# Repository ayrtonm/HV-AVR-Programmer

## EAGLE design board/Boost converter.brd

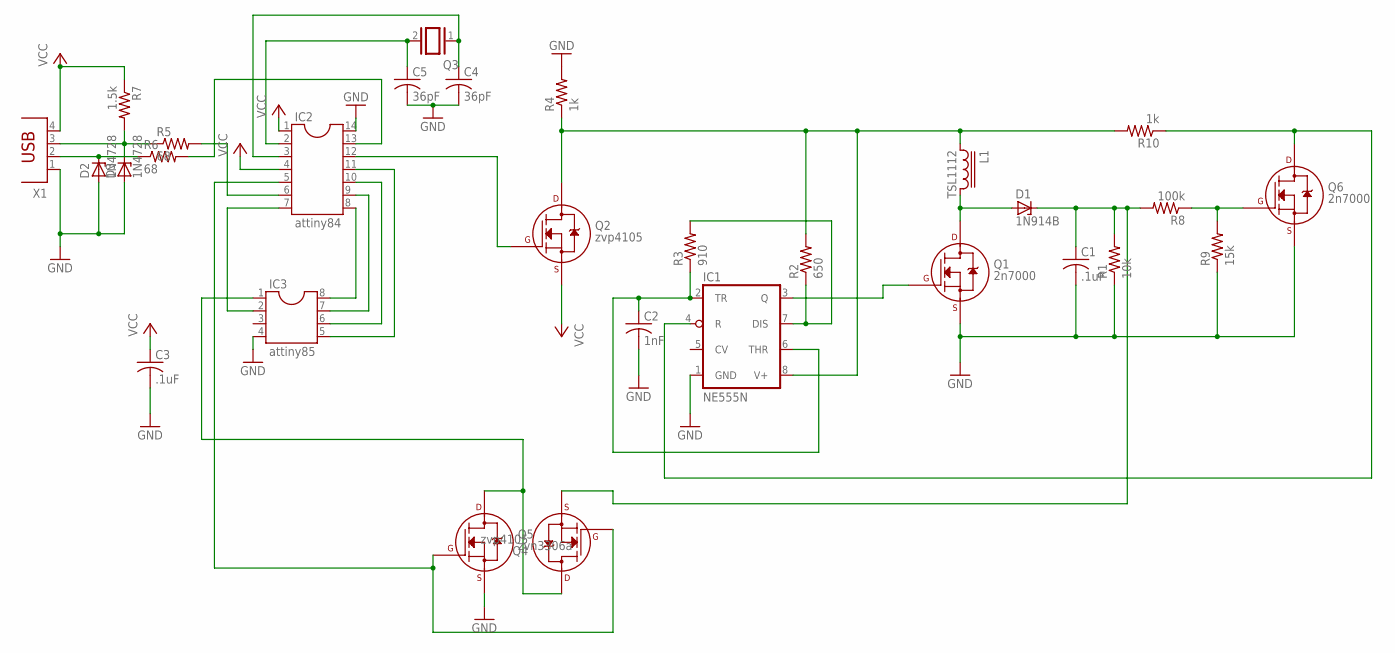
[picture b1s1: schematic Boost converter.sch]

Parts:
C1, C3: .1uF; C025-024X044
C2: 1nF; C025-024X044
C4, C5: 36pF; C025-024X044
D1: 1N914B; DO41Z10
D2, D3: 1N4728; DO41Z10
IC1: NE555N; DIL08-ROUND
IC2: attiny84; DIL14
IC3: attiny85; SOCKET-08
L1: TSL1112
Q1, Q6: 2n7000; TO-92
Q2, Q4: zvp4105; TO-92
Q3: XTAL/S; QS
Q5: zvn3306a; TO-92
R1: 10k; 0204/7
R2: 650; 0204/7
R3: 910; 0204/7
R4, R10: 1k; 0204/7
R5, R6: 68; 0204/7
R7: 1.5k; 0204/7
R8: 100k; 0204/7
R9: 15k; 0204/7
X1: PN87520

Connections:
GND: C1.2, C2.2, C3.2, C4.2, C5.2, D2.A, D3.A, IC1.1 (GND), IC2.14, IC3.4, Q1.1 (S), Q5.1 (S), Q6.1 (S), R1.1, R4.2, R9.1, X1.1
unnamed: D2.C, R6.1, X1.2
unnamed: C5.1, IC2.2, Q3.2
unnamed: C4.1, IC2.3, Q3.1
unnamed: D3.C, R5.1, R7.2, X1.3
unnamed: IC2.6, R5.2
unnamed: IC2.13, R6.2
unnamed: IC1.8 (V+), L1.1, Q2.3 (D), R2.2, R4.1, R10.2
unnamed: Q6.2 (G), R8.1, R9.2
unnamed: IC1.4 (R), Q6.3 (D), R10.1
unnamed: IC2.12, Q2.2 (G)
unnamed: C1.1, D1.C, Q4.1 (S), R1.2, R8.2
unnamed: IC1.3 (Q), Q1.2 (G)
unnamed: IC1.7 (DIS), R2.1, R3.2
unnamed: C2.1, IC1.2 (TR), IC1.6 (THR), R3.1
unnamed: D1.A, L1.2, Q1.3 (D)
unnamed: IC3.1, Q4.3 (D), Q5.3 (D)
unnamed: IC2.5, Q4.2 (G), Q5.2 (G)
unnamed: IC2.8, IC3.8
unnamed: IC2.9, IC3.7
unnamed: IC2.10, IC3.6
unnamed: IC2.11, IC3.5
unnamed: IC2.7, IC3.2
VCC: C3.1, IC2.1, IC2.4, Q2.1 (S), R7.1, X1.4

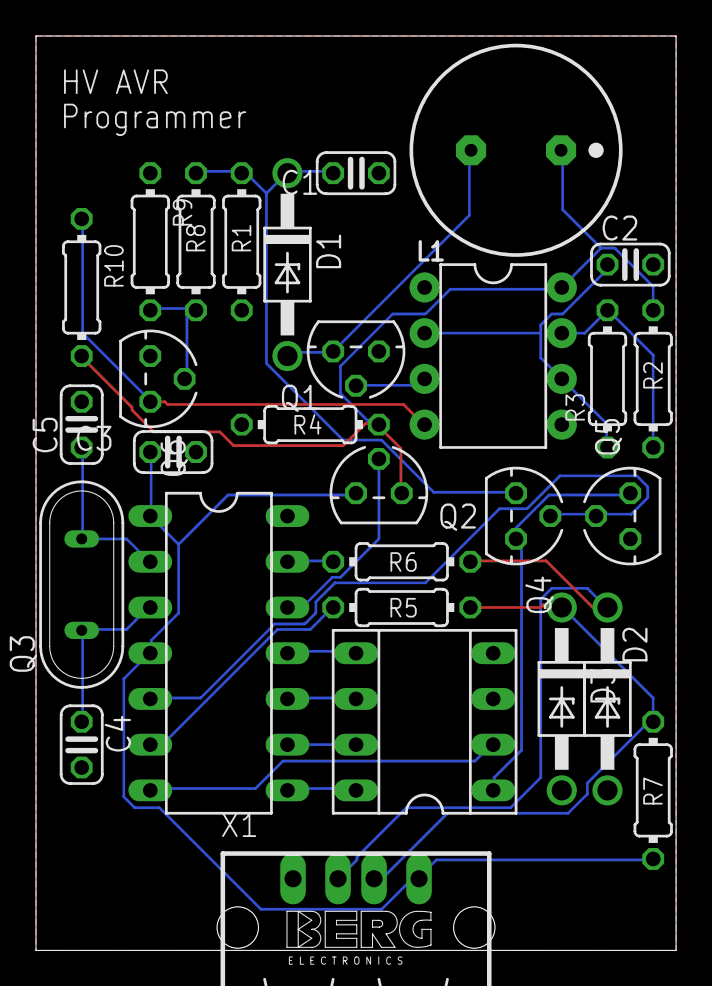
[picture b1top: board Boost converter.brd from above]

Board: 2 copper layers, 35.6 x 50.8 mm, 29 parts (0 on the bottom side), 24 nets.

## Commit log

2015-01-21 First commit
    need to disconnect usb data lines from those pins of the ic and add crystal
    oscillator to ic
2015-01-24 Rerouted USB data lines
    rerouted usb D- line to pin 6 on the attiny84 socket and D+ line to pin 5(int0) on attiny84 socket. pins 2 and 3 on socket were left unconnected but I still need to add crystal oscillator to board an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
2015-01-24 Added crystal oscillator
    also had to move around boost converter components to make room for the oscillator, not sure how drastic the inductance and capacitance changes from the pcb lines will be and if it will have a large 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
2015-01-24 added v-usb library and done routing board
    added v-usb library, but still need to change settings in usbconfig.h. also usb needs to use only one port for both d+ and d- lines (d+ can't be on pa0 and d- on pb1) so I had to change the usb data 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
2015-01-25 Removed unnecessary files
2015-01-27 Started HV serial programming
2015-01-30 Updated hv.c
    added functions and commands for writing the fuse bits, but still not sure how to write the actual data
2015-01-30 Fuse bit write functions should now work
    fuse bit data is sent on SDI in second data transfer. I should add other features such as reading fuse bits.
2015-01-31 Added makefile and V-USB
2015-01-31 First version of host software
    usbconfig.h modified to work with PCINT0 and PA7 and PA0
    host software writes default ATtiny85 fuse bits then exits by default
    remember to invert fuse bits when using write_xfuse_bits()
2015-01-31 Now fuse bits are inverted
2015-01-31 Added crystal oscillator and potentiometer to board
    crystal oscillator is next to ATtiny84 and potentiometer is next to inductor and 555. also moved around boost converter components so they are located in the same places as in the first version of th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
2015-02-05 Modified V-USB settings to work with attiny84
    slight modifications to hv.c and main.c. device code now compiles without errors. also remember to use 12 MHz crystal while flashing the chip
2015-02-05 Turn off boost converter on reset
2015-02-05 Added host makefile
2015-02-16 ATtiny84 recognized through usb
    using 12 MHz crystal oscillator with Cf = 18 pF and 2 36 pF caps to ground make sure to not have too much stray capacitance
2015-02-18 Board Version 2
    Updated board to include crystal oscillator and caps, boost converter feedback loop with resistor divider and mosfet inverter to trigger 555 reset pin and cmos for supplying 12V to t85 reset pin. Dim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
2015-02-22 Added control for supply to t85 reset pin
    added a cmos inverter to control supply to t85 reset pin and changed boost converter so it's directly driven by the t84
2015-05-19 Added Spice simulation files
    added simulation.asc and zvp4105a.sub. I'm trying to make the simulation as accurate as possible to get a better understanding of what is happening since I don't have an oscilloscope to debug with. z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

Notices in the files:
parts and their libraries:
inductors-tdk: Copyright (C) 2008, Bob Starr
